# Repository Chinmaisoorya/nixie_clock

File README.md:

# 170V Nixie Tube Boost Converter

This is a custom PCB designed from scratch in KiCad 8. It takes a 5V input and boosts it up to 170V DC to power Nixie tubes. 

## The Design
* **Controller:** MC34063 
* **Switch:** External N-Channel MOSFET (for high voltage handling)
* **Layout:** 2-Layer PCB with a full bottom-layer Ground Plane for noise reduction.
* **High Voltage Routing:** Thick traces with high clearance for the 170V output.

## Project Status
* [x] Schematic (ERC Clean)
* [x] PCB Layout (DRC Clean)
* [x] 3D Render Complete
* [ ] Physical Manufacturing (Coming soon)

## 3D Render

## Gerber
* [x] Gerber Files Generated (nixie_clock-B_Cu.zip)

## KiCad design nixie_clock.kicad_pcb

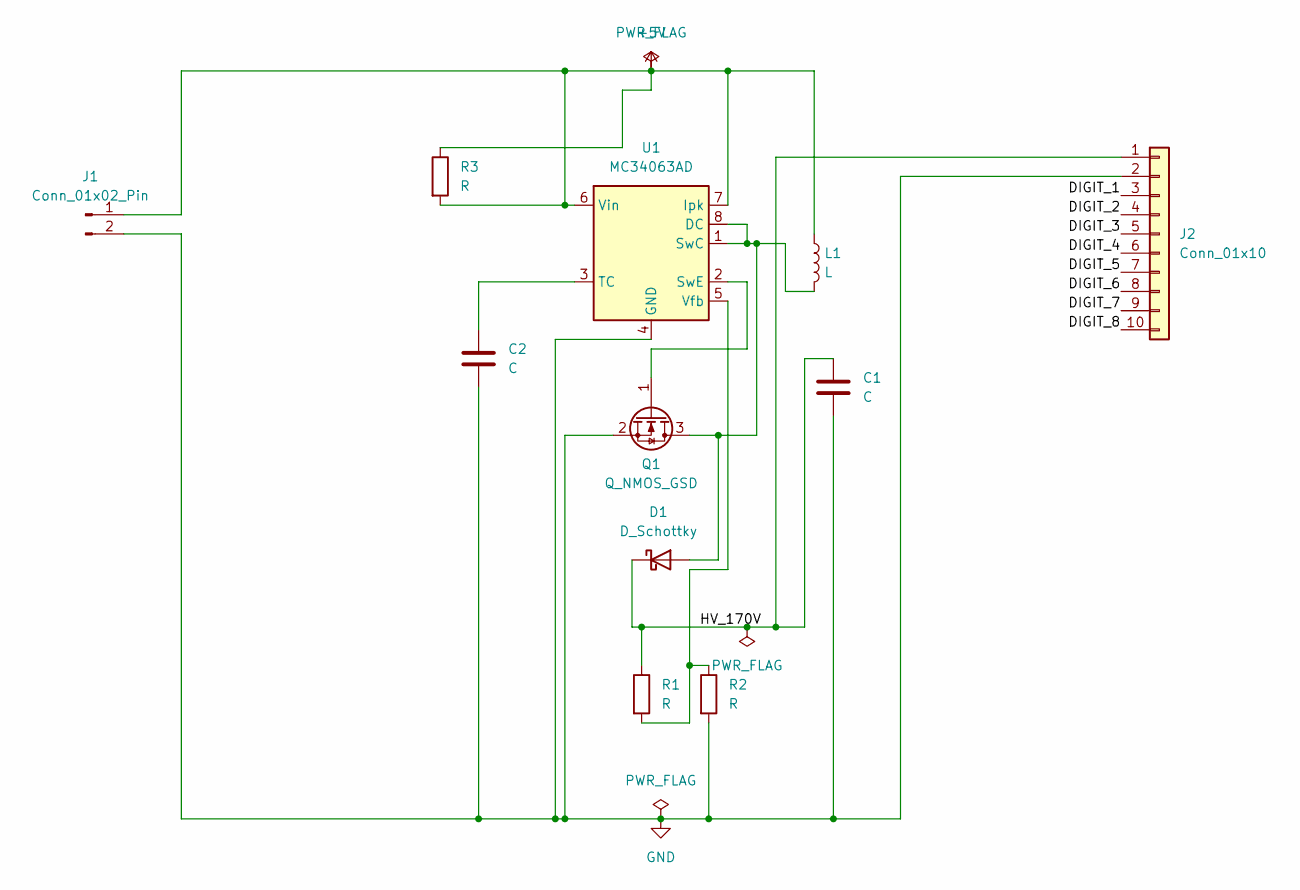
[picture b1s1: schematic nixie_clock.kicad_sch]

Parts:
C1, C2: C; C_0805_2012Metric
D1: D_Schottky; D_SMA
J1: Conn_01x02_Pin; PinHeader_1x02_P2.54mm_Vertical
J2: Conn_01x10; PinHeader_1x10_P2.54mm_Vertical
L1: L; L_1210_3225Metric
Q1: Q_NMOS_GSD; SOT-23
R1, R2, R3: R; R_0805_2012Metric
U1: MC34063AD; SOIC-8_3.9x4.9mm_P1.27mm

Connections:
+5V: J1.1, L1.1, R3.1, R3.2, U1.6 (Vin), U1.7 (Ipk)
/DIGIT_1: J2.3
/DIGIT_2: J2.4
/DIGIT_3: J2.5
/DIGIT_4: J2.6
/DIGIT_5: J2.7
/DIGIT_6: J2.8
/DIGIT_7: J2.9
/DIGIT_8: J2.10
/HV_170V: C1.1, D1.1 (K), J2.1, R1.1
GND: C1.2, C2.2, J1.2, J2.2, Q1.2 (S), R2.2, U1.4 (GND)
unnamed: D1.2 (A), L1.2, Q1.3 (D), U1.1 (SwC), U1.8 (DC)
unnamed: Q1.1 (G), U1.2 (SwE)
unnamed: C2.1, U1.3 (TC)
unnamed: R1.2, R2.1, U1.5 (Vfb)

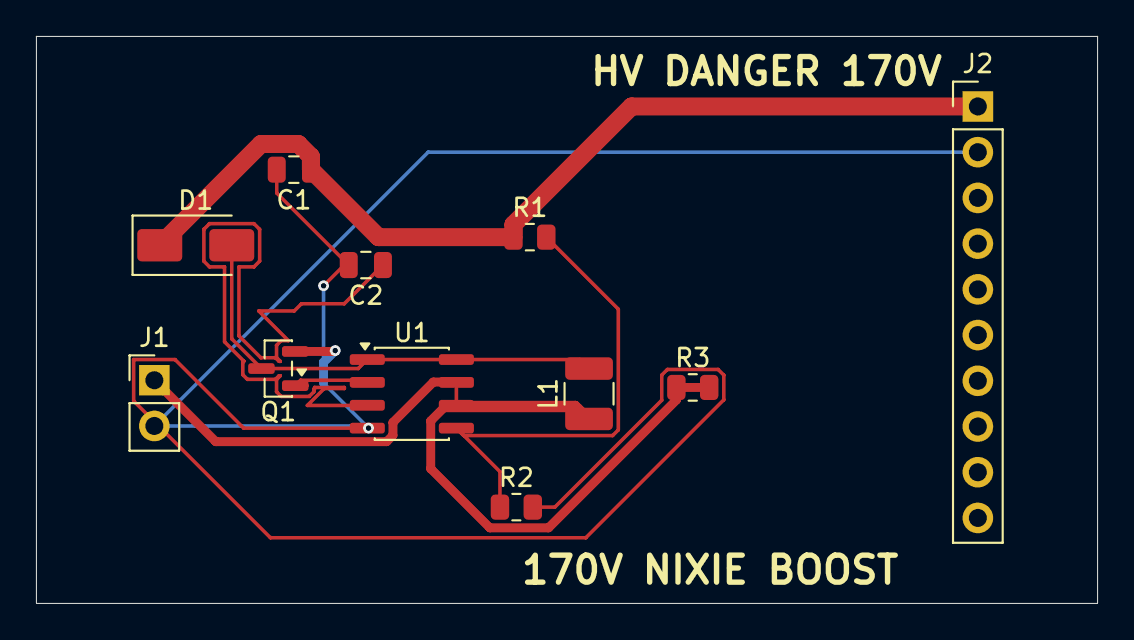
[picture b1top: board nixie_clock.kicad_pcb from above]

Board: 2 copper layers, 58.9 x 31.5 mm, 11 parts (0 on the bottom side), 7 nets.
